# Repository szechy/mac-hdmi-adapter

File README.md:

## Mac Classic HDMI adapter board

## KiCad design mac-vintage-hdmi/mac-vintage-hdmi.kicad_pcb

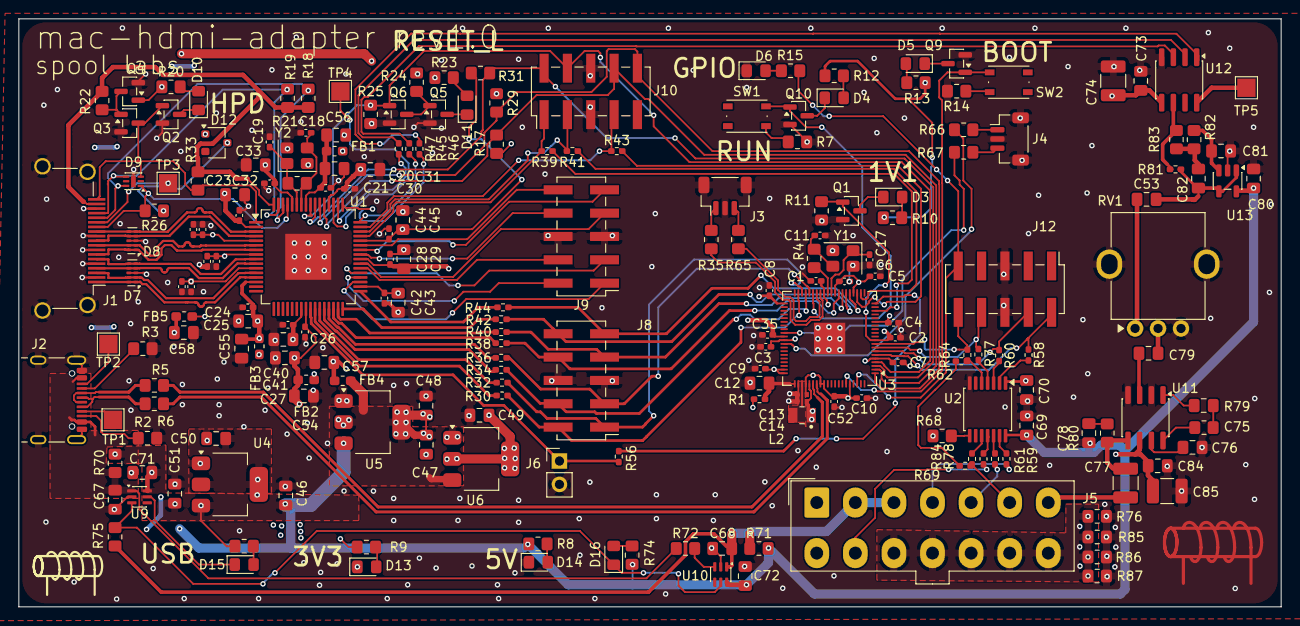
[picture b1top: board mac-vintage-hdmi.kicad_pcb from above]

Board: 4 copper layers, 137.4 x 64.0 mm, 207 parts (0 on the bottom side), 154 nets.

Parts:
C1, C2, C3, C4, C5, C6, C7, C8, C9, C10, C35, C37, C39, C52, C83: 100nF; C_0402_1005Metric_Pad0.74x0.62mm_HandSolder
C11, C17: 15pF; C_0402_1005Metric_Pad0.74x0.62mm_HandSolder
C12: 4.7uF; C_0805_2012Metric_Pad1.18x1.45mm_HandSolder
C13, C14: 4.7uF; generic_capc1005x50_wide
C18, C19: 27pF; C_0402_1005Metric_Pad0.74x0.62mm_HandSolder
C20, C23, C25, C27, C29, C31, C33, C41, C43, C45, C69, C70, C73, C75, C80, C85: 100nF; C_0805_2012Metric_Pad1.18x1.45mm_HandSolder
C21, C22, C24, C26, C28, C30, C32, C34, C36, C38, C40, C42, C44: 10nF; C_0402_1005Metric_Pad0.74x0.62mm_HandSolder
C46, C47, C48, C49, C50, C51, C53, C54, C55, C56, C57, C58, C76, C79: 10uF; C_0805_2012Metric_Pad1.18x1.45mm_HandSolder
C67, C68, C71, C72: 1uF; C_0805_2012Metric_Pad1.18x1.45mm_HandSolder
C74, C77, C84: 47uF; C_1210_3225Metric_Pad1.33x2.70mm_HandSolder
C78: 47nF; C_0805_2012Metric_Pad1.18x1.45mm_HandSolder
C81: 470pF; C_0805_2012Metric_Pad1.18x1.45mm_HandSolder
C82: 1nF; C_0805_2012Metric_Pad1.18x1.45mm_HandSolder
D3, D13, D14: Red; LED_0805_2012Metric_Pad1.15x1.40mm_HandSolder
D4, D5, D6, D10, D11: Green; LED_0805_2012Metric_Pad1.15x1.40mm_HandSolder
D7, D8: RCLAMP0524PATCT; USON-10_2.5x1.0mm_P0.5mm
D9: RCLAMP0504P; MLF-6-1EP_1.6x1.6mm_P0.5mm_EP0.5x1.26mm
D12: MA3X704A; SC-59
D15, D16: Yellow; LED_0805_2012Metric_Pad1.15x1.40mm_HandSolder
FB1, FB2, FB3, FB4, FB5: BLM18KG601SN1D; L_0603_1608Metric_Pad1.05x0.95mm_HandSolder
J1: HDMI_A; HDMI_A_Amphenol_10029449-x01xLF_Horizontal
J2: TYPE-C-31-M-12; USB_C_Receptacle_HRO_TYPE-C-31-M-12
J3, J4: BM03B-SRSS-TB; JST_SH_BM03B-SRSS-TB_1x03-1MP_P1.00mm_Vertical
J5: 39-28-1143; Molex_Mini-Fit_Jr_5566-14A_2x07_P4.20mm_Vertical
J6: HX PZ2.54-1x2P ZZ; PinHeader_1x02_P2.54mm_Vertical
J8, J9, J10, J12: Conn_02x05_Odd_Even; PinHeader_2x05_P2.54mm_Vertical_SMD
L2: AOTA-B201610S3R3-101-T; L_Abracon_AOTA-B201610S3R3-101-T_2.0x1.6mm
Q1: Si2342DS; SOT-23
Q2, Q3, Q4, Q5, Q6, Q9, Q10: BSS123LT1; SOT-23
R1, R30, R32, R34, R36, R38, R39, R40, R41, R42, R43, R44, R45, R46, R47, R56: 33; R_0402_1005Metric_Pad0.72x0.64mm_HandSolder
R2, R3, R79: 5.1k; R_0805_2012Metric_Pad1.20x1.40mm_HandSolder
R4, R7, R9, R14, R33, R75: 1k; R_0805_2012Metric_Pad1.20x1.40mm_HandSolder
R5, R6: 27; R_0805_2012Metric_Pad1.20x1.40mm_HandSolder
R8, R10, R12, R13, R15, R17, R20, R23, R29, R31, R73, R74: 2.7k; R_0805_2012Metric_Pad1.20x1.40mm_HandSolder
R11: 10k; R_0805_2012Metric_Pad1.20x1.40mm_HandSolder
R18, R19: 47k; R_0805_2012Metric_Pad1.20x1.40mm_HandSolder
R21: 390k; R_0805_2012Metric_Pad1.20x1.40mm_HandSolder
R22, R24, R25: 100k; R_0805_2012Metric_Pad1.20x1.40mm_HandSolder
R26: 27k; R_0805_2012Metric_Pad1.20x1.40mm_HandSolder
R35, R65, R66, R67: 100; R_0805_2012Metric_Pad1.20x1.40mm_HandSolder
R58, R59, R60, R61, R62, R64, R69, R77, R78, R81, R84: 0; R_0402_1005Metric_Pad0.72x0.64mm_HandSolder
R68, R70, R71, R72, R76, R85, R86, R87: 0; R_0805_2012Metric_Pad1.20x1.40mm_HandSolder
R80: 47; R_0805_2012Metric_Pad1.20x1.40mm_HandSolder
R82: 13k; R_0805_2012Metric_Pad1.20x1.40mm_HandSolder
R83: 8.2k; R_0805_2012Metric_Pad1.20x1.40mm_HandSolder
RV1: PTV09A; Potentiometer_Bourns_PTV09A_RearMount
SW1, SW2: 434133025816; SW_Push_1P1T_NO_Vertical_Wuerth_434133025816
TP1, TP2, TP3, TP4, TP5: TestPoint; TestPoint_Pad_2.0x2.0mm
U1: ADV7611BSWZ; LQFP-64-1EP_10x10mm_P0.5mm_EP5x5mm
U2: TXU0104PWR; TSSOP-14_4.4x5mm_P0.65mm
U3: RP2354B; QFN-80-1EP_10x10mm_P0.4mm_EP3.4x3.4mm
U4, U5: NCP1117-3.3_SOT223; SOT-223-3_TabPin2
U6: NCP1117ST18T3G; SOT-223-3_TabPin2
U9, U10: LM66100DCKR; SOT-363_SC-70-6
U11: LM386M-1; SOIC-8_3.9x4.9mm_P1.27mm
U12: TM8211-TA2302; SOIC-8_3.9x4.9mm_P1.27mm
U13: TLV9061IDBVR; SOT-23-5
Y1: ABM8-272-T3; Crystal_SMD_Abracon_ABM8G-4Pin_3.2x2.5mm
Y2: ABM8-28.63636MHZ-B2-T; Crystal_SMD_Abracon_ABM8G-4Pin_3.2x2.5mm

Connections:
+1V1: C1.1, C2.1, C3.1, C14.1, L2.1, Q1.1 (G), R11.1, U3.10 (DVDD), U3.32 (DVDD), U3.51 (DVDD), U3.65 (VREG_FB)
+3V3: C4.1, C5.1, C6.1, C7.1, C8.1, C9.1, C10.1, C13.1, C35.1, C50.1, C52.1, C70.1, C73.1, C74.1, D12.1 (A), R1.1, R9.1, R17.1, R29.1, U2.1 (VCCA), U3.5 (IOVDD), U3.15 (IOVDD), U3.24 (IOVDD), U3.29 (IOVDD), U3.41 (IOVDD), U3.50 (IOVDD), U3.59 (ADC_AVDD), U3.60 (IOVDD), U3.64 (VREG_VIN), U3.68 (USB_OTP_VDD), U3.69 (QSPI_IOVDD), U3.76 (IOVDD), U4.2 (VO), U12.5 (VDD)
+5V: C46.1, C51.1, C69.1, C71.1, C72.1, C80.1, Q3.1 (G), R8.1, R10.1, R12.1, R13.1, R20.1, R23.1, R24.1, R68.1, R70.2, R71.2, R73.1, R74.1, U2.14 (VCCB), U4.3 (VI), U5.3 (VI), U9.6 (VOUT), U10.6 (VOUT), U13.5 (V+)
+5V_HDMI: J1.18 (+5V), R18.1, R19.1, R22.1, R33.1, U1.64 (RXA_5V)
+5V_MAC: C68.1, J5.2, J5.3, R71.1, R75.1, U10.1 (VIN)
+5V_USB: C67.1, J2.A4/B9 (VBUS), J2.B4/A9 (VBUS), R70.1, R72.1, U9.1 (VIN)
+12V_MAC: C84.1, C85.2, J5.1, U11.6 (V+)
/Data/ADV7611_CB0CR0: J9.10, U1.43 (P0)
/Data/ADV7611_CB1CR1: J9.9, U1.42 (P1)
/Data/ADV7611_CB2CR2: J9.8, U1.41 (P2)
/Data/ADV7611_CB3CR3: J9.7, U1.39 (P3)
/Data/ADV7611_CB4CR4: J9.4, U1.38 (P4)
/Data/ADV7611_CB5CR5: J9.3, U1.37 (P5)
/Data/ADV7611_CB6CR6: J9.2, U1.36 (P6)
/Data/ADV7611_CB7CR7: J9.1, U1.35 (P7)
/Data/ADV7611_DE: J10.1, R39.1, U1.45 (DE)
/Data/ADV7611_DE_RP2350: R39.2, U3.18 (GPIO18)
/Data/ADV7611_HS: J10.3, R41.1, U1.46 (HS)
/Data/ADV7611_HS_RP2350: R41.2, U3.22 (GPIO22)
/Data/ADV7611_INT1: J10.2, R31.2, U1.55 (INT1), U3.3 (GPIO6)
/Data/ADV7611_LLC: J6.1, R56.1, U1.25 (LLC)
/Data/ADV7611_LLC_RP2350: R56.2, U3.20 (GPIO20)
/Data/ADV7611_RESET_L: J10.4, Q6.1 (G), R25.1, U1.56 (~RESET), U3.4 (GPIO7)
/Data/ADV7611_VS: J10.7, R43.1, U1.47 (VS/FIELD/ALSB)
/Data/ADV7611_VS_RP2350: R43.2, U3.23 (GPIO23)
/Data/ADV7611_Y0: R44.1, U1.33 (P8)
/Data/ADV7611_Y0_RP2350: J8.9, R44.2, U3.25 (GPIO24)
/Data/ADV7611_Y1: R42.1, U1.32 (P9)
/Data/ADV7611_Y1_RP2350: J8.10, R42.2, U3.26 (GPIO25)
/Data/ADV7611_Y2: R40.1, U1.31 (P10)
/Data/ADV7611_Y2_RP2350: J8.7, R40.2, U3.27 (GPIO26)
/Data/ADV7611_Y3: R38.1, U1.30 (P11)
/Data/ADV7611_Y3_RP2350: J8.8, R38.2, U3.28 (GPIO27)
/Data/ADV7611_Y4: R36.1, U1.29 (P12)
/Data/ADV7611_Y4_RP2350: J8.3, R36.2, U3.36 (GPIO28)
/Data/ADV7611_Y5: R34.1, U1.28 (P13)
/Data/ADV7611_Y5_RP2350: J8.4, R34.2, U3.37 (GPIO29)
/Data/ADV7611_Y6: R32.1, U1.27 (P14)
/Data/ADV7611_Y6_RP2350: J8.1, R32.2, U3.38 (GPIO30)
/Data/ADV7611_Y7: R30.1, U1.26 (P15)
/Data/ADV7611_Y7_RP2350: J8.2, R30.2, U3.39 (GPIO31)
/Data/HDMI_CEC: D9.1 (IO1), J1.13 (CEC), R26.2, U1.61 (CEC)
/Data/HDMI_CLK_N: D8.5 (IO4), D8.6 (NC), J1.12 (CK-), U1.3 (RXA_C-)
/Data/HDMI_CLK_P: D8.4 (IO3), D8.7 (NC), J1.10 (CK+), U1.4 (RXA_C+)
/Data/HDMI_DDC_SCL: D9.6 (IO4), J1.15 (SCL), R18.2, U1.62 (DDCA_SCL)
/Data/HDMI_DDC_SDA: D9.4 (IO3), J1.16 (SDA), R19.2, U1.63 (DDCA_SDA)
/Data/HDMI_HPD: D9.3 (IO2), J1.19 (HPD), Q2.1 (G), Q4.3 (D), R33.2, U1.1 (HPA_A/INT2)
/Data/HDMI_LN0_N: D8.2 (IO2), D8.9 (NC), J1.9 (D0-), U1.6 (RXA_0-)
/Data/HDMI_LN0_P: D8.1 (IO1), D8.10 (NC), J1.7 (D0+), U1.7 (RXA_0+)
/Data/HDMI_LN1_N: D7.5 (IO4), D7.6 (NC), J1.6 (D1-), U1.9 (RXA_1-)
/Data/HDMI_LN1_P: D7.4 (IO3), D7.7 (NC), J1.4 (D1+), U1.10 (RXA_1+)
/Data/HDMI_LN2_N: D7.2 (IO2), D7.9 (NC), J1.3 (D2-), U1.12 (RXA_2-)
/Data/HDMI_LN2_P: D7.1 (IO1), D7.10 (NC), J1.1 (D2+), U1.13 (RXA_2+)
/Data/I2C_ADV7611_SCL: J10.8, R17.2, U1.53 (SCL), U3.2 (GPIO5)
/Data/I2C_ADV7611_SDA: J10.10, R29.2, U1.54 (SDA), U3.1 (GPIO4)
/Data/I2S_ADV7611_DOUT_R: R45.1, U1.48 (AP)
/Data/I2S_ADV7611_LRCLK_R: R47.1, U1.50 (LRCLK)
/Data/I2S_ADV7611_SCLK_R: R46.1, U1.49 (SCLK/INT2)
/Data/RP2350_BOOTSEL: Q9.1 (G), SW2.4, U3.75 (~QSPI_SS)
/Data/RP2350_GPIO_LED: J12.9, R15.1, U3.78 (GPIO1)
/Data/RP2350_RUN: Q10.1 (G), SW1.3, U3.35 (RUN)
/Data/SWD_RP2350_SWCLK: R35.1, U3.33 (SWCLK)
/Data/SWD_RP2350_SWDIO: R65.1, U3.34 (SWDIO)
/Data/UART_RP2350_RX: R66.1, U3.52 (GPIO41/ADC1)
/Data/UART_RP2350_TX: R67.1, U3.49 (GPIO40/ADC0)
/Data/USB2_D_R_N: R5.2, U3.66 (USB_DM)
/Data/USB2_D_R_P: R6.2, U3.67 (USB_DP)
/Data/VREG_AVDD: C12.1, R1.2, U3.61 (VREG_AVDD)
/Power/5V_MAC_ST_L: D16.1 (K), R75.2, U9.3 (~CE), U10.5 (ST)
/Power/5V_USB_ST_L: D15.1 (K), U9.5 (ST)
/Power/+1V8_ADV7611: C49.1, FB1.1, FB2.1, FB3.1, U6.2 (VO)
/Power/+3V3_ADV7611: C47.1, C48.1, FB4.1, FB5.1, U5.2 (VO), U6.3 (VI)
/Power/J5_GND: J5.10, J5.11, J5.12, J5.13, J5.14, R76.1, R85.1, R86.1, R87.1
/Power/MAC_HSYNC_3V3: R60.2, U2.3 (A2)
/Power/MAC_HSYNC_5V: J5.5, R61.2
/Power/MAC_PWM_3V3: R77.2, U2.4 (A3)
/Power/MAC_PWM_5V: J5.9, R78.2
/Power/MAC_SOUND: C77.1, J5.7
/Power/MAC_VIDOUT: R64.2, R69.1
/Power/MAC_VIDOUT_3V3: R62.2, R64.1, U2.5 (A4)
/Power/MAC_VIDOUT_5V: J5.6, R69.2, R84.2
/Power/MAC_VSYNC_3V3: R58.2, U2.2 (A1)
/Power/MAC_VSYNC_5V: J5.4, R59.2
/Power/USB2_CC1: J2.A5 (CC1), R3.1
/Power/USB2_CC2: J2.B5 (CC2), R2.1
/Power/USB2_SBU1: J2.A8 (SBU1), TP1.1 (1_1)
/Power/USB2_SBU2: J2.B8 (SBU2), TP2.1 (1_1)
ADV7611_CVDD_1V8: C22.1, C23.1, C24.1, C25.1, C55.1, FB3.2, U1.2 (CVDD), U1.14 (CVDD)
ADV7611_DVDDIO_3V3: C40.1, C41.1, C42.1, C43.1, C44.1, C45.1, C57.1, FB4.2, R31.1, U1.23 (DVDDIO), U1.34 (DVDDIO), U1.44 (DVDDIO)
ADV7611_DVDD_1V8: C26.1, C27.1, C28.1, C29.1, C30.1, C31.1, C32.1, C33.1, C54.1, FB2.2, U1.24 (DVDD), U1.40 (DVDD), U1.52 (DVDD), U1.60 (DVDD)
ADV7611_PVDD_1V8: C20.1, C21.1, C56.1, FB1.2, U1.57 (PVDD)
ADV7611_TVDD_3V3: C34.1, C36.1, C37.1, C38.1, C39.1, C58.1, C83.1, FB5.2, U1.5 (TVDD), U1.8 (TVDD), U1.11 (TVDD)
GND: C1.2, C2.2, C3.2, C4.2, C5.2, C6.2, C7.2, C8.2, C9.2, C10.2, C11.2, C12.2, C13.2, C14.2, C17.1, C18.1, C19.1, C20.2, C21.2, C22.2, C23.2, C24.2, C25.2, C26.2, C27.2, C28.2, C29.2, C30.2, C31.2, C32.2, C33.2, C34.2, C35.2, C36.2, C37.2, C38.2, C39.2, C40.2, C41.2, C42.2, C43.2, C44.2, C45.2, C46.2, C47.2, C48.2, C49.2, C50.2, C51.2, C52.2, C54.2, C55.2, C56.2, C57.2, C58.2, C67.2, C68.2, C69.2, C70.2, C71.2, C72.2, C73.2, C74.2, C76.1, C78.2, C80.2, C81.2, C83.2, C84.2, C85.1, D6.1 (K), D7.3 (GND), D7.8 (GND), D8.3 (GND), D8.8 (GND), D9.7 (GND), D13.1 (K), D14.1 (K), J1.2 (D2S), J1.5 (D1S), J1.8 (D0S), J1.11 (CKS), J1.17 (GND), J1.SH, J2.A1/B12 (GND), J2.B1/A12 (GND), J2.S1 (SHIELD), J2.S2 (SHIELD), J2.S3 (SHIELD), J2.S4 (SHIELD), J3.2, J3.MP1 (MountPin_1), J3.MP2 (MountPin_2), J4.2, J4.MP1 (MountPin_1), J4.MP2 (MountPin_2), J6.2, J8.5, J8.6, J9.5, J9.6, J10.5, J10.6, J12.5, J12.6, Q1.2 (S), Q2.2 (S), Q3.2 (S), Q4.2 (S), Q5.2 (S), Q6.2 (S), Q9.2 (S), Q10.2 (S), R2.2, R3.2, R7.2, R11.2, R14.2, R25.2, R76.2, R85.2, R86.2, R87.2, RV1.3, RV1.4 (MP), RV1.5 (MP), U1.65 (GND), U2.7 (GND), U3.62 (VREG_PGND), U3.81 (GND), U4.1 (GND), U5.1 (GND), U6.1 (GND), U9.2 (GND), U10.2 (GND), U11.2 (-), U11.4 (GND), U12.4 (GND), U13.2 (V-), Y1.2 (G), Y1.4 (G), Y2.2 (G), Y2.4 (G)
I2S_ADV7611_DOUT: R45.2, U12.3 (DIN)
I2S_ADV7611_LRCLK: R47.2, U12.2 (WS)
I2S_ADV7611_SCLK: R46.2, U12.1 (BCK)
MAC_HSYNC_3V3_RP2350: J12.4, R60.1, U3.7 (GPIO9)
MAC_PWM_3V3_RP2350: J12.8, R77.1, U3.8 (GPIO10)
MAC_VIDOUT_3V3_RP2350: J12.10, R62.1, U3.9 (GPIO11)
MAC_VSYNC_3V3_RP2350: J12.2, R58.1, U3.6 (GPIO8)
unnamed: C11.1, R4.2, Y1.3
unnamed: C53.1, RV1.1
unnamed: C75.1, R79.2
unnamed: C75.2, U11.1 (GAIN)
unnamed: C77.2, R80.1, U11.5
unnamed: C78.1, R80.2
unnamed: C79.2, RV1.2
unnamed: C82.2, R82.2, R83.1
unnamed: D3.2 (A), R10.2
unnamed: D3.1 (K), Q1.3 (D)
unnamed: D4.2 (A), R12.2
unnamed: D4.1 (K), Q10.3 (D)
unnamed: D5.2 (A), R13.2
unnamed: D5.1 (K), Q9.3 (D)
unnamed: D6.2 (A), R15.2
unnamed: D10.2 (A), R20.2
unnamed: D10.1 (K), Q2.3 (D)
unnamed: D11.2 (A), R23.2
unnamed: D11.1 (K), Q5.3 (D)
unnamed: D12.3 (K), R26.1
unnamed: D13.2 (A), R9.2
unnamed: D14.2 (A), R8.2
unnamed: D15.2 (A), R73.2
unnamed: D16.2 (A), R74.2
unnamed: J1.14 (UTILITY), TP3.1 (1_1)
unnamed: J3.1, R35.2
unnamed: J3.3, R65.2
unnamed: J4.1, R66.2
unnamed: J4.3, R67.2
unnamed: Q3.3 (D), Q4.1 (G), R22.2
unnamed: Q5.1 (G), Q6.3 (D), R24.2
unnamed: R7.1, SW1.1
unnamed: R14.1, SW2.2
unnamed: R79.1, U11.8 (GAIN)
unnamed: TP4.1 (1_1), U1.51 (MCLK/INT2)
unnamed: C19.2, R21.2, U1.59 (XTALN), Y2.1
unnamed: C18.2, R21.1, U1.58 (XTALP), Y2.3
unnamed: R59.1, U2.13 (B1Y)
unnamed: R61.1, U2.12 (B2Y)
unnamed: R78.1, U2.11 (B3Y)
unnamed: R84.1, U2.10 (B4Y)
unnamed: R68.2, U2.8 (OE)
unnamed: L2.2, U3.63 (VREG_LX)
unnamed: C17.2, U3.30 (XIN), Y1.1
unnamed: R4.1, U3.31 (XOUT)
unnamed: R72.2, U10.3 (~CE)
unnamed: C79.1, U11.3 (+)
unnamed: C76.2, U11.7 (BYPASS)
unnamed: R81.1, R82.1, U12.6 (LCH)
unnamed: TP5.1 (1_1), U12.8 (RCH)
unnamed: C81.1, R83.2, U13.3 (+)
unnamed: C53.2, C82.1, R81.2, U13.1, U13.4 (-)
USB2_D_N: J2.A7 (D-), J2.B7 (D-), R5.1
USB2_D_P: J2.A6 (D+), J2.B6 (D+), R6.1

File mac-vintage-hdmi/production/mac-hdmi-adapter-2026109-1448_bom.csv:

Designator,Footprint,Quantity,Value,LCSC Part #
"C1, C10, C2, C3, C35, C4, C5, C52, C6, C7, C8, C9",0402,12,100n,
"C11, C17",0402,2,15pF,
C12,0805,1,4.7uF,
"C13, C14",generic_capc1005x50_wide,2,4.7uF,
"C18, C19",0402,2,27pF,
"C20, C23, C25, C27, C29, C31, C33, C41, C43, C45, C69, C70, C73, C80, C85",0805,15,0.1uF,
"C21, C22, C24, C26, C28, C30, C32, C34, C36, C38, C40, C42, C44",0402,13,10nF,
"C37, C39, C83",0402,3,0.1uF,
"C46, C47, C48, C49, C50, C51, C53, C54, C55, C56, C57, C58, C79",0805,13,10uF,
"C67, C68, C71, C72",0805,4,1uF,
"C74, C77, C84",1210,3,47uF,
C78,0805,1,47nF,
C81,0805,1,470pF,
C82,0805,1,1nF,
"D10, D11, D4, D5, D6",0805,5,Green,LG R971-KN-1-0-20-R18
D12,SC-59,1,MA3X704A,
"D13, D14, D3",0805,3,Red,LS R976-NR-1-0-20-R18
"D15, D16",0805,2,Yellow,LY R976-PS-36-0-20-R18
"D7, D8",USON-10_2.5x1.0mm_P0.5mm,2,RCLAMP0524PA,
D9,MLF-6-1EP_1.6x1.6mm_P0.5mm_EP0.5x1.26mm,1,RCLAMP0504P,
"FB1, FB2, FB3, FB4, FB5",0603,5,BLM18KG601SN1D,
J1,HDMI_A_Amphenol_10029449-x01xLF_Horizontal,1,HDMI_A,
"J10, J12, J8, J9",PinHeader_2x05_P2.54mm_Vertical_SMD,4,Conn_02x05_Odd_Even,
J2,USB_C_Receptacle_HRO_TYPE-C-31-M-12,1,TYPE-C-31-M-12,
"J3, J4",JST_SH_BM03B-SRSS-TB_1x03-1MP_P1.00mm_Vertical,2,BM03B-SRSS-TB,
J5,Molex_Mini-Fit_Jr_5566-14A_2x07_P4.20mm_Vertical,1,39-28-1143,
J6,PinHeader_1x02_P2.54mm_Vertical_SMD_Pin1Left,1,Conn_01x02,
L2,L_Abracon_AOTA-B201610S3R3-101-T_2.0x1.6mm,1,AOTA-B201610S3R3-101-T,
Q1,SOT-23,1,Si2342DS,
"Q10, Q2, Q3, Q4, Q5, Q6, Q9",SOT-23,7,BSS123LT1,
"R1, R30, R32, R34, R36, R38, R39, R40, R41, R42, R43, R44, R45, R46, R47, R56",0402,16,33,
"R10, R12, R13, R15, R2, R20, R23, R3, R73, R74, R8, R9",0805,12,5.1k,
"R14, R33, R4, R7, R75",0805,5,1K,
"R17, R29, R31",0805,3,2.7k,
"R18, R19",0805,2,47k,
"R22, R24, R25",0805,3,100k,
R26,0805,1,27k,
"R35, R65, R66, R67",0805,4,100,
"R5, R6",0805,2,27,
"R58, R59, R60, R61, R62, R77, R78, R84",0402,8,0,
"R68, R72, R76, R85, R86, R87",0805,6,0,
R80,0805,1,47,
R82,0805,1,13k,
R83,0805,1,8.2k,
RV1,Potentiometer_Bourns_PTV09A_RearMount,1,PTV09A,
"SW1, SW2",SW_Push_1P1T_NO_Vertical_Wuerth_434133025816,2,434133025816,
"TP1, TP2, TP3, TP4, TP5",TestPoint_Pad_2.0x2.0mm,5,TestPoint,
U1,LQFP-64-1EP_10x10mm_P0.5mm_EP5x5mm,1,ADV7611,
"U10, U9",SOT-363_SC-70-6,2,LM66100DCKR,
U11,SOIC-8_3.9x4.9mm_P1.27mm,1,LM386M-1,
U12,SOIC-8_3.9x4.9mm_P1.27mm,1,PT8211-S,
U13,SOT-23-5,1,TLV9061IDBVR,
U2,TSSOP-14_4.4x5mm_P0.65mm,1,TXU0104PWR,
U3,QFN-80-1EP_10x10mm_P0.4mm_EP3.4x3.4mm,1,RP2354B,
"U4, U5",SOT-223-3_TabPin2,2,NCP1117-3.3_SOT223,
U6,SOT-223-3_TabPin2,1,NCP1117ST18T3G,
Y1,Crystal_SMD_Abracon_ABM8G-4Pin_3.2x2.5mm,1,ABM8-272-T3,
Y2,Crystal_SMD_Abracon_ABM8G-4Pin_3.2x2.5mm,1,ABM8-28.63636MHZ-B2-T,
